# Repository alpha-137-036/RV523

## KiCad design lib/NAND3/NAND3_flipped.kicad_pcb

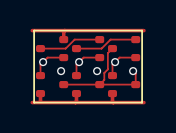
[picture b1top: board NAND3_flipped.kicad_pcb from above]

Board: 2 copper layers, 6 parts (0 on the bottom side), 7 nets.

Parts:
N1, N2, N3: NMOS; SOT523
P1, P2, P3: PMOS; SOT523

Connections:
A1: N1.1 (G), P1.1 (G)
A2: N2.1 (G), P2.1 (G)
A3: N3.1 (G), P3.1 (G)
VDD: P1.2 (S), P2.2 (S), P3.2 (S)
Y: N3.3 (D), P1.3 (D), P2.3 (D), P3.3 (D)
int1: N1.3 (D), N2.2 (S)
int2: N2.3 (D), N3.2 (S)

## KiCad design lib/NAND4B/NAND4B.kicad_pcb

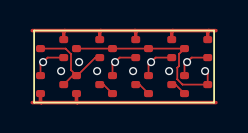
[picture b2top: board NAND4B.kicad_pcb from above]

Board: 2 copper layers, 10 parts (0 on the bottom side), 11 nets.

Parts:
nand4.N1, nand4.N2, nand4.N3, nand4.N4: NMOS; SOT523
nand4.P1, nand4.P2, nand4.P3, nand4.P4: PMOS; SOT523
not1.N1: NMOS; SOT523
not1.P1: PMOS; SOT523

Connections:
A1: nand4.N1.1 (G), nand4.P1.1 (G), not1.N1.3 (D), not1.P1.3 (D)
A1_N: not1.N1.1 (G), not1.P1.1 (G)
A2: nand4.N2.1 (G), nand4.P2.1 (G)
A3: nand4.N3.1 (G), nand4.P3.1 (G)
A4: nand4.N4.1 (G), nand4.P4.1 (G)
GND: nand4.N1.2 (S), not1.N1.2 (S)
VDD: nand4.P1.2 (S), nand4.P2.2 (S), nand4.P3.2 (S), nand4.P4.2 (S), not1.P1.2 (S)
Y: nand4.N4.3 (D), nand4.P1.3 (D), nand4.P2.3 (D), nand4.P3.3 (D), nand4.P4.3 (D)
nand4.int1: nand4.N1.3 (D), nand4.N2.2 (S)
nand4.int2: nand4.N2.3 (D), nand4.N3.2 (S)
nand4.int3: nand4.N3.3 (D), nand4.N4.2 (S)

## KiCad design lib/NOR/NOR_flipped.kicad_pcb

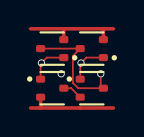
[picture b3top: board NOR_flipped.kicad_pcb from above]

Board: 2 copper layers, 4 parts (0 on the bottom side), 5 nets.

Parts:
N1, N2: SOT-523
P1, P2: SOT-523

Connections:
A: N1.1 (G), P1.1 (G)
B: N2.1 (G), P2.1 (G)
C: P1.3 (D), P2.2 (S)
GND: N1.2 (S), N2.2 (S)
Y: N1.3 (D), N2.3 (D), P2.3 (D)
